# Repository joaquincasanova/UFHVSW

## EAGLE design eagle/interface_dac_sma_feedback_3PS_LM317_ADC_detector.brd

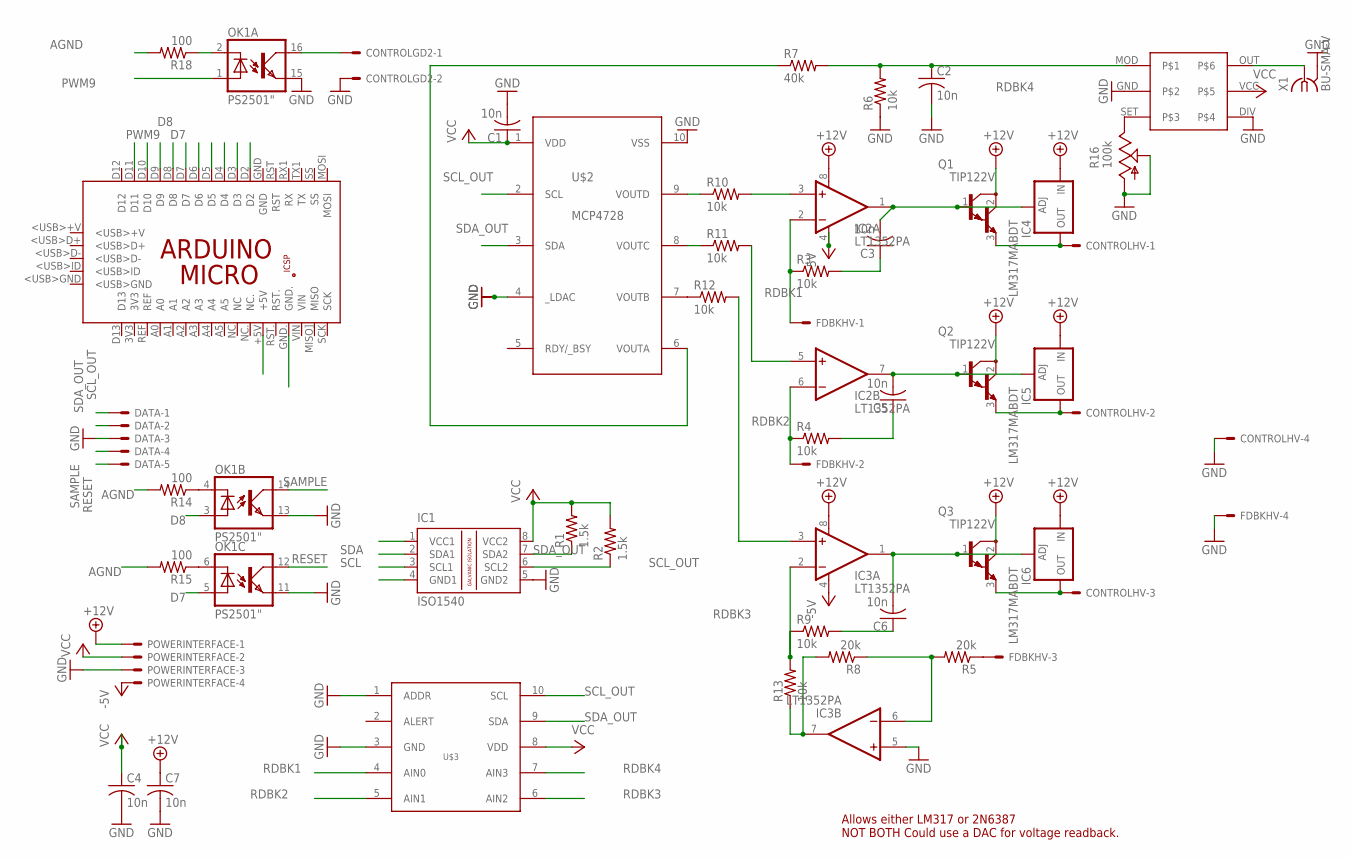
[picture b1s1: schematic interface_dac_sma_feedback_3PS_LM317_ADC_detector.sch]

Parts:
C1, C2, C3, C4, C5, C6, C7: 10n; C050-024X044
CONTROLGD2: KK-156-2
CONTROLHV: KK-156-4
DATA: KK-156-5
FDBKHV: KK-156-4
IC1: ISO1540; DIL08
IC2, IC3: LT1352PA; DIL08
IC4, IC5, IC6: LM317MABDT; DPACK
OK1: PS2501"; DIL16
PCB1: ARDUINO_MICRO
POWERINTERFACE: KK-156-4
Q1, Q2, Q3: TIP122V; TO220V
R1, R2: 1.5k; 0207/12
R3, R4, R6, R9, R10, R11, R12, R13: 10k; 0207/12
R5, R8: 20k; 0207/12
R7: 40k; 0207/12
R14, R15, R18: 100; 0207/12
R16: 100k; SP19L
U$1: LTC6992; DIL06
U$2: MCP4728DIL; DIL10
U$3: ADS1015DIL; DIL10
X1: BU-SMA-V

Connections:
+12V: C7.1, IC2.8 (V+), IC3.8 (V+), IC4.3 (IN), IC5.3 (IN), IC6.3 (IN), POWERINTERFACE.1, Q1.2 (C), Q2.2 (C), Q3.2 (C)
-5V: IC2.4 (V-), IC3.4 (V-), POWERINTERFACE.4
A+5: IC1.1 (VCC1), PCB1.+5V
AGND: IC1.4 (GND1), PCB1.GND., R14.2, R15.2, R18.2
D4: PCB1.D4
D7: OK1.5 (A), PCB1.D7
D8: OK1.3 (A), PCB1.D8
D10: PCB1.D10
D11: PCB1.D11
ENSW2: CONTROLGD2.1, OK1.16 (COL)
GND: C1.2, C2.2, C4.2, C7.2, CONTROLGD2.2, CONTROLHV.4, DATA.3, FDBKHV.4, IC1.5 (GND2), IC3.5 (+IN), OK1.11 (EMI), OK1.13 (EMI), OK1.15 (EMI), POWERINTERFACE.3, R6.1, R16.A, R16.S, U$1.DIV, U$1.GND, U$2.4 (_LDAC), U$2.10 (VSS), U$3.1 (ADDR), U$3.3 (GND), X1.2, X1.3 (2), X1.4 (2), X1.5 (2)
unnamed: R7.1, U$2.6 (VOUTA)
unnamed: OK1.4 (C), R14.1
unnamed: C3.1, R3.2
unnamed: CONTROLHV.1, IC4.4 (OUT), Q1.3 (E)
unnamed: CONTROLHV.3, IC6.4 (OUT), Q3.3 (E)
unnamed: OK1.6 (C), R15.1
unnamed: OK1.2 (C), R18.1
unnamed: FDBKHV.3, R5.1
unnamed: C5.2, IC2.7 (OUT), IC5.1 (ADJ), Q2.1 (B)
unnamed: CONTROLHV.2, IC5.4 (OUT), Q2.3 (E)
unnamed: R16.E, U$1.SET
unnamed: U$1.OUT, X1.1
unnamed: IC3.7 (OUT), R8.2, R13.1
unnamed: C5.1, R4.2
unnamed: IC2.3 (+IN), R10.2
unnamed: IC2.5 (+IN), R11.2
unnamed: IC3.3 (+IN), R12.2
unnamed: C3.2, IC2.1 (OUT), IC4.1 (ADJ), Q1.1 (B)
unnamed: C6.1, R9.2
unnamed: C6.2, IC3.1 (OUT), IC6.1 (ADJ), Q3.1 (B)
unnamed: IC3.6 (-IN), R5.2, R8.1
unnamed: R10.1, U$2.9 (VOUTD)
unnamed: R12.1, U$2.7 (VOUTB)
unnamed: R11.1, U$2.8 (VOUTC)
PWM5: PCB1.D5
PWM6: PCB1.D6
PWM9: OK1.1 (A), PCB1.D9
RDBK1: FDBKHV.1, IC2.2 (-IN), R3.1, U$3.4 (AIN0)
RDBK2: FDBKHV.2, IC2.6 (-IN), R4.1, U$3.5 (AIN1)
RDBK3: IC3.2 (-IN), R9.1, R13.2, U$3.6 (AIN2)
RDBK4: C2.1, R6.2, R7.2, U$1.MOD, U$3.7 (AIN3)
RESET: DATA.5, OK1.12 (COL)
SAMPLE: DATA.4, OK1.14 (COL)
SCL: IC1.3 (SCL1), PCB1.D3
SCL_OUT: DATA.1, IC1.6 (SCL2), R2.1, U$2.2 (SCL), U$3.10 (SCL)
SDA: IC1.2 (SDA1), PCB1.D2
SDA_OUT: DATA.2, IC1.7 (SDA2), R1.1, U$2.3 (SDA), U$3.9 (SDA)
VCC: C1.1, C4.1, IC1.8 (VCC2), POWERINTERFACE.2, R1.2, R2.2, U$1.VCC, U$2.1 (VDD), U$3.8 (VDD)

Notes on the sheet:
Allows either LM317 or 2N6387 NOT BOTH Could use a DAC for voltage readback.

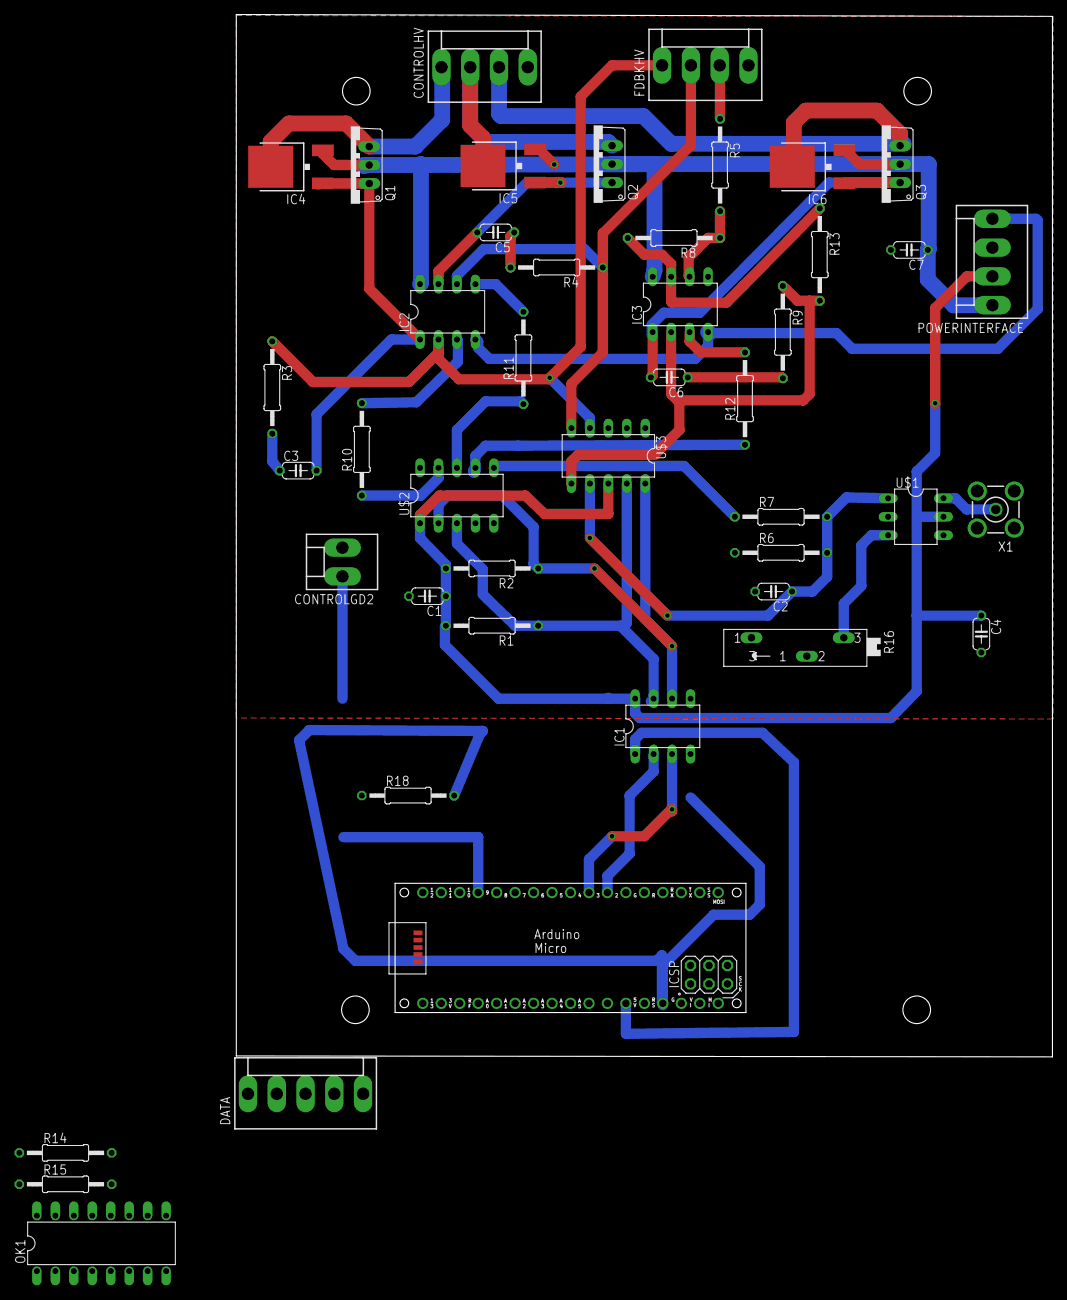
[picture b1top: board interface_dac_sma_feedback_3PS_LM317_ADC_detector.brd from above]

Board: 2 copper layers, 112.3 x 143.4 mm, 44 parts (0 on the bottom side), 44 nets.

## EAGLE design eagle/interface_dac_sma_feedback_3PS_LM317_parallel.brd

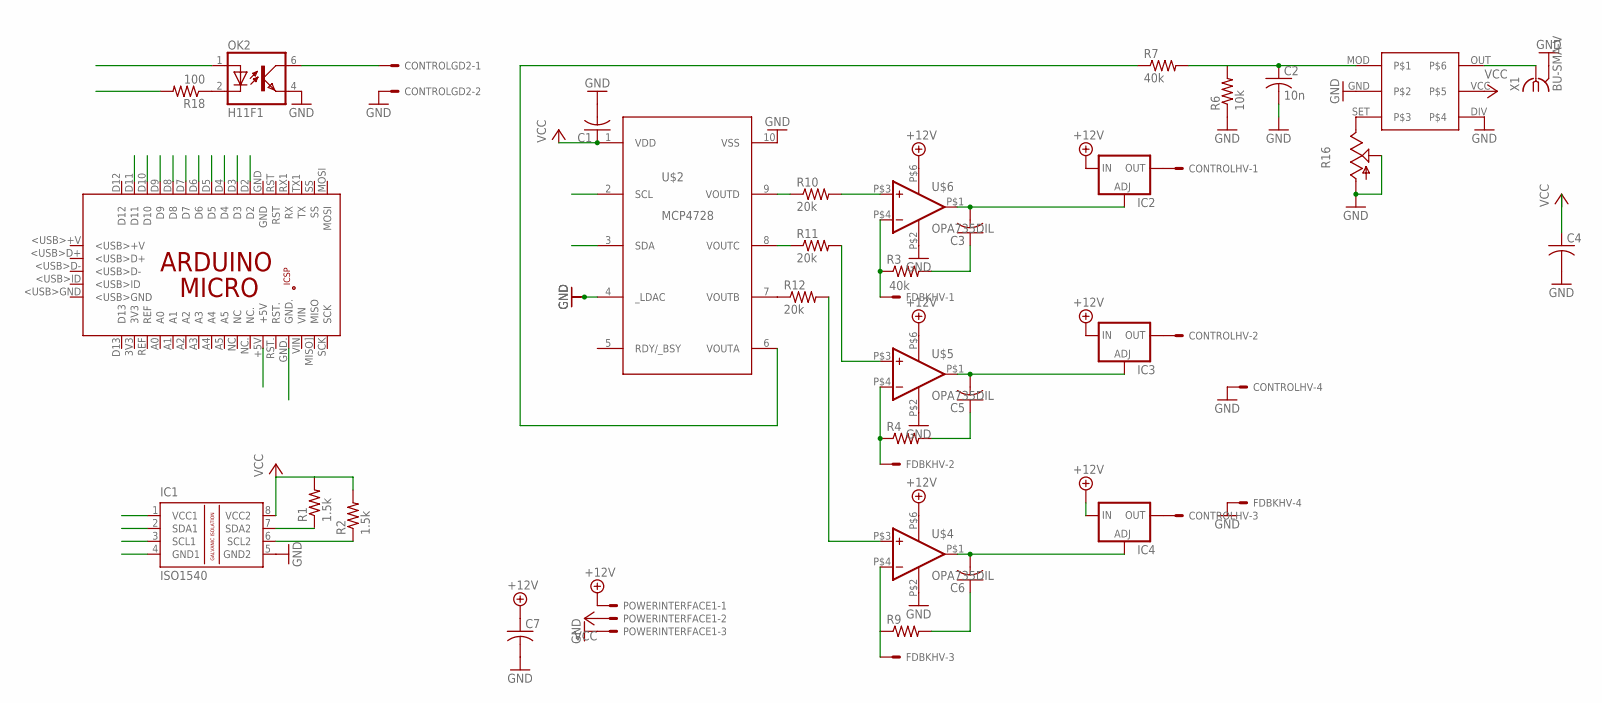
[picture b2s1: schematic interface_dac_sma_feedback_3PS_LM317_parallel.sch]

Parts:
C1, C7: C-US050-050X075; C050-050X075
C2: 10n; C050-024X044
C3, C5, C6: C-US050-024X044; C050-024X044
C4: C-US075-063X106; C075-063X106
CONTROLGD2: KK-156-2
CONTROLHV: KK-156-4
FDBKHV: 40k; KK-156-4
IC1: ISO1540; DIL08
IC2, IC3, IC4: LM317TS; 317TS
OK2: H11F1; DIL05
PCB1: ARDUINO_MICRO
POWERINTERFACE1: KK-156-3
R1, R2: 1.5k; 0207/12
R3, R4, R9: R-US_0207/12; 0207/12
R6: 10k; 0207/12
R7: 40k; 0207/12
R10, R11, R12: 20k; 0207/12
R16: TRIM_US-B90P; SP19L
R18: 100; 0207/12
U$1: LTC6992; DIL06
U$2: MCP4728DIL; DIL10
U$4, U$5, U$6: OPA735DIL; DIL6
X1: BU-SMA-V

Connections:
+12V: C7.1, IC2.3 (IN), IC3.3 (IN), IC4.3 (IN), POWERINTERFACE1.1, U$4.P$6 (V+), U$5.P$6 (V+), U$6.P$6 (V+)
A+5: IC1.1 (VCC1), PCB1.+5V
AGND: IC1.4 (GND1), PCB1.GND., R18.2
D4: PCB1.D4
D7: PCB1.D7
D8: PCB1.D8
D10: PCB1.D10
D11: PCB1.D11
ENSW2: CONTROLGD2.1, OK2.6 (COL)
GND: C1.2, C2.2, C4.2, C7.2, CONTROLGD2.2, CONTROLHV.4, FDBKHV.4, IC1.5 (GND2), OK2.4 (EMIT), POWERINTERFACE1.3, R6.1, R16.A, R16.S, U$1.DIV, U$1.GND, U$2.4 (_LDAC), U$2.10 (VSS), U$4.P$2 (V-), U$5.P$2 (V-), U$6.P$2 (V-), X1.2, X1.3 (2), X1.4 (2), X1.5 (2)
unnamed: R7.1, U$2.6 (VOUTA)
unnamed: C2.1, R6.2, R7.2, U$1.MOD
unnamed: C3.1, R3.2
unnamed: CONTROLHV.1, IC2.2 (OUT)
unnamed: CONTROLHV.3, IC4.2 (OUT)
unnamed: FDBKHV.2, R4.1, U$5.P$4 (-IN)
unnamed: OK2.2 (C), R18.1
unnamed: FDBKHV.1, R3.1, U$6.P$4 (-IN)
unnamed: C5.2, IC3.1 (ADJ), U$5.P$1 (OUT)
unnamed: CONTROLHV.2, IC3.2 (OUT)
unnamed: R16.E, U$1.SET
unnamed: U$1.OUT, X1.1
unnamed: FDBKHV.3, R9.1, U$4.P$4 (-IN)
unnamed: C5.1, R4.2
unnamed: R10.2, U$6.P$3 (+IN)
unnamed: R11.2, U$5.P$3 (+IN)
unnamed: R12.2, U$4.P$3 (+IN)
unnamed: C3.2, IC2.1 (ADJ), U$6.P$1 (OUT)
unnamed: C6.1, R9.2
unnamed: C6.2, IC4.1 (ADJ), U$4.P$1 (OUT)
unnamed: R10.1, U$2.9 (VOUTD)
unnamed: R12.1, U$2.7 (VOUTB)
unnamed: R11.1, U$2.8 (VOUTC)
PWM5: PCB1.D5
PWM6: PCB1.D6
PWM9: OK2.1 (A), PCB1.D9
SCL: IC1.3 (SCL1), PCB1.D3
SCL_OUT: IC1.6 (SCL2), R2.1, U$2.2 (SCL)
SDA: IC1.2 (SDA1), PCB1.D2
SDA_OUT: IC1.7 (SDA2), R1.1, U$2.3 (SDA)
VCC: C1.1, C4.1, IC1.8 (VCC2), POWERINTERFACE1.2, R1.2, R2.2, U$1.VCC, U$2.1 (VDD)

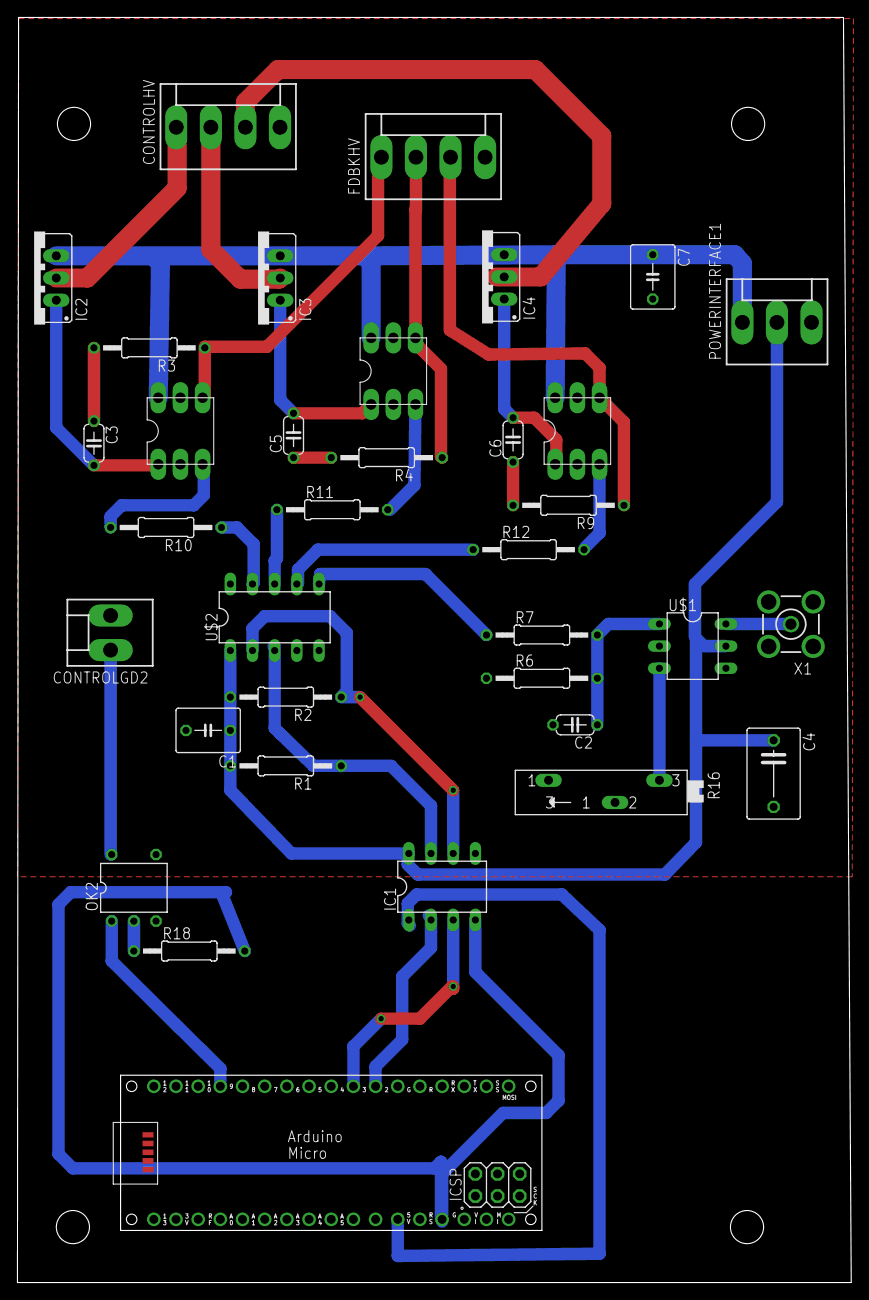
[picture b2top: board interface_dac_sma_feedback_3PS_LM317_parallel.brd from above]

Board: 2 copper layers, 95.5 x 144.9 mm, 35 parts (0 on the bottom side), 34 nets.

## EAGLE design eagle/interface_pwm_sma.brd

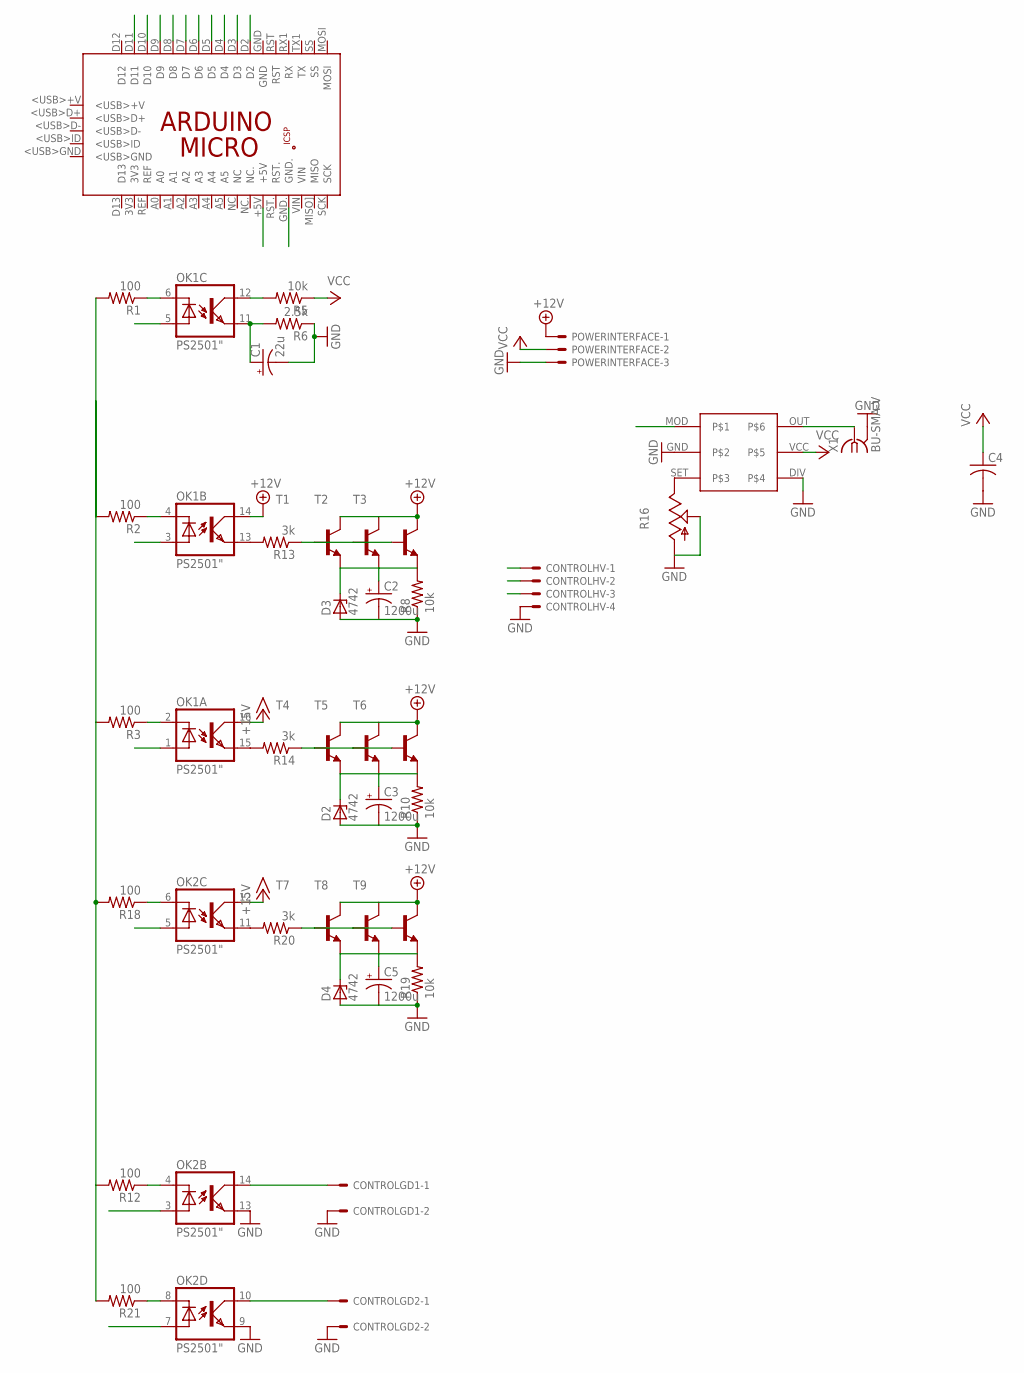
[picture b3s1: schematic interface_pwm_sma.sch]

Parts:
C1: 22u; E5-10,5
C2, C3, C5: 1200u; EB20D
C4: C-US075-063X106; C075-063X106
CONTROLGD1, CONTROLGD2: KK-156-2
CONTROLHV: KK-156-4
D2, D3, D4: 4742; ZDIO-10
OK1, OK2: PS2501"; DIL16
PCB1: ARDUINO_MICRO
POWERINTERFACE: KK-156-3
R1, R2, R3, R12, R18, R21: 100; 0207/12
R5: 10k; 0207/15
R6: 2.5k; 0207/12
R8, R10, R19: 10k; 0207/12
R13, R14, R20: 3k; 0207/15
R16: TRIM_US-B90P; SP19L
T1, T2, T3, T4, T5, T6, T7, T8, T9: 2N2222-NPN-TO92-EBC; TO92-EBC
U$1: LTC6992; DIL06
X1: BU-SMA-V

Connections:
+15V: OK1.14 (COL), OK1.16 (COL), OK2.12 (COL), POWERINTERFACE.1, T1.C, T2.C, T3.C, T4.C, T5.C, T6.C, T7.C, T8.C, T9.C
A+5: PCB1.+5V
AGND: PCB1.GND., R1.2, R2.2, R3.2, R12.2, R18.2, R21.2
D2: PCB1.D2
D4: PCB1.D4
D7: PCB1.D7
D8: OK2.7 (A), PCB1.D8
D10: OK2.3 (A), PCB1.D10
D11: PCB1.D11
ENSW1: CONTROLGD1.1, OK2.14 (COL)
ENSW2: CONTROLGD2.1, OK2.10 (COL)
GND: C1.-, C2.-, C3.-, C4.2, C5.-, CONTROLGD1.2, CONTROLGD2.2, CONTROLHV.4, D2.A, D3.A, D4.A, OK2.9 (EMI), OK2.13 (EMI), POWERINTERFACE.3, R6.1, R8.1, R10.1, R16.A, R16.S, R19.1, U$1.DIV, U$1.GND, X1.2, X1.3 (2), X1.4 (2), X1.5 (2)
unnamed: OK2.4 (C), R12.1
unnamed: OK1.12 (COL), R5.2
unnamed: OK1.6 (C), R1.1
unnamed: OK1.4 (C), R2.1
unnamed: OK1.15 (EMI), R14.2
unnamed: OK2.6 (C), R18.1
unnamed: R20.1, T7.B, T8.B, T9.B
unnamed: OK2.8 (C), R21.1
unnamed: OK1.2 (C), R3.1
unnamed: R16.E, U$1.SET
unnamed: U$1.OUT, X1.1
unnamed: OK1.13 (EMI), R13.2
unnamed: R13.1, T1.B, T2.B, T3.B
unnamed: R14.1, T4.B, T5.B, T6.B
unnamed: OK2.11 (EMI), R20.2
PWM3: OK1.5 (A), PCB1.D3
PWM5: OK1.3 (A), PCB1.D5
PWM6: OK1.1 (A), PCB1.D6
PWM9: OK2.5 (A), PCB1.D9
PWMOUT: C1.+, OK1.11 (EMI), R6.2, U$1.MOD
VCC: C4.1, POWERINTERFACE.2, R5.1, U$1.VCC
VREG1: C2.+, CONTROLHV.1, D3.C, R8.2, T1.E, T2.E, T3.E
VREG2: C3.+, CONTROLHV.2, D2.C, R10.2, T4.E, T5.E, T6.E
VREG3: C5.+, CONTROLHV.3, D4.C, R19.2, T7.E, T8.E, T9.E

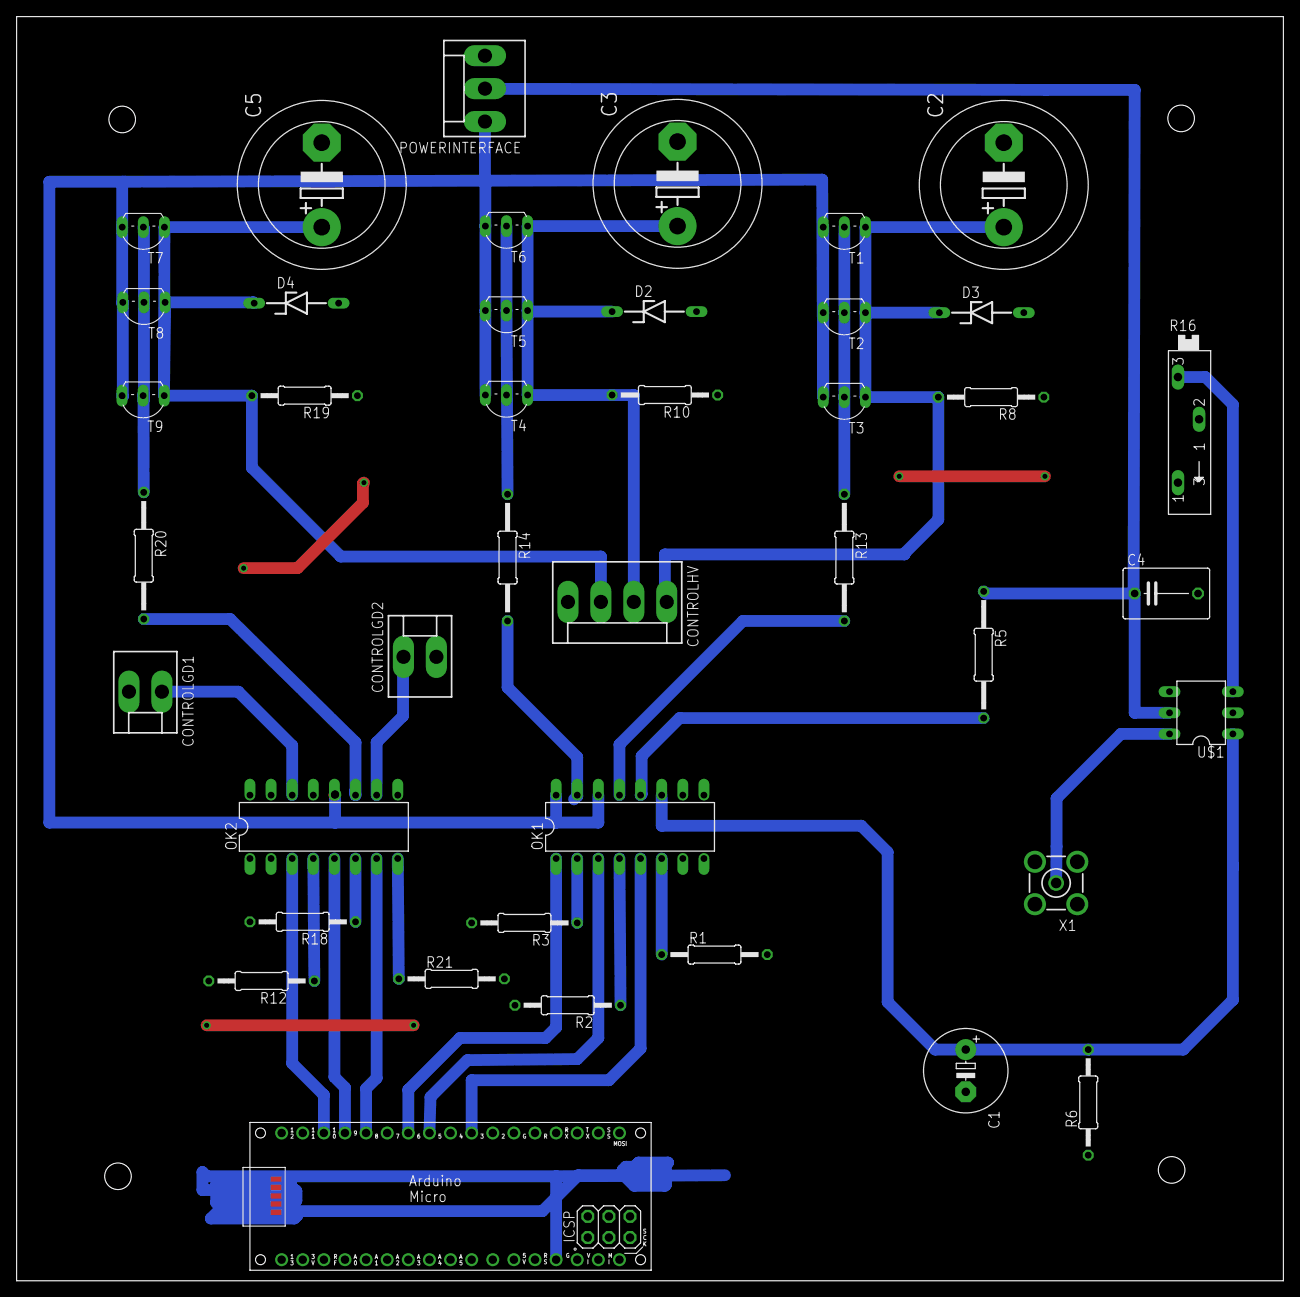
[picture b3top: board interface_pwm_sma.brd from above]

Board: 2 copper layers, 152.4 x 152.1 mm, 41 parts (0 on the bottom side), 31 nets.

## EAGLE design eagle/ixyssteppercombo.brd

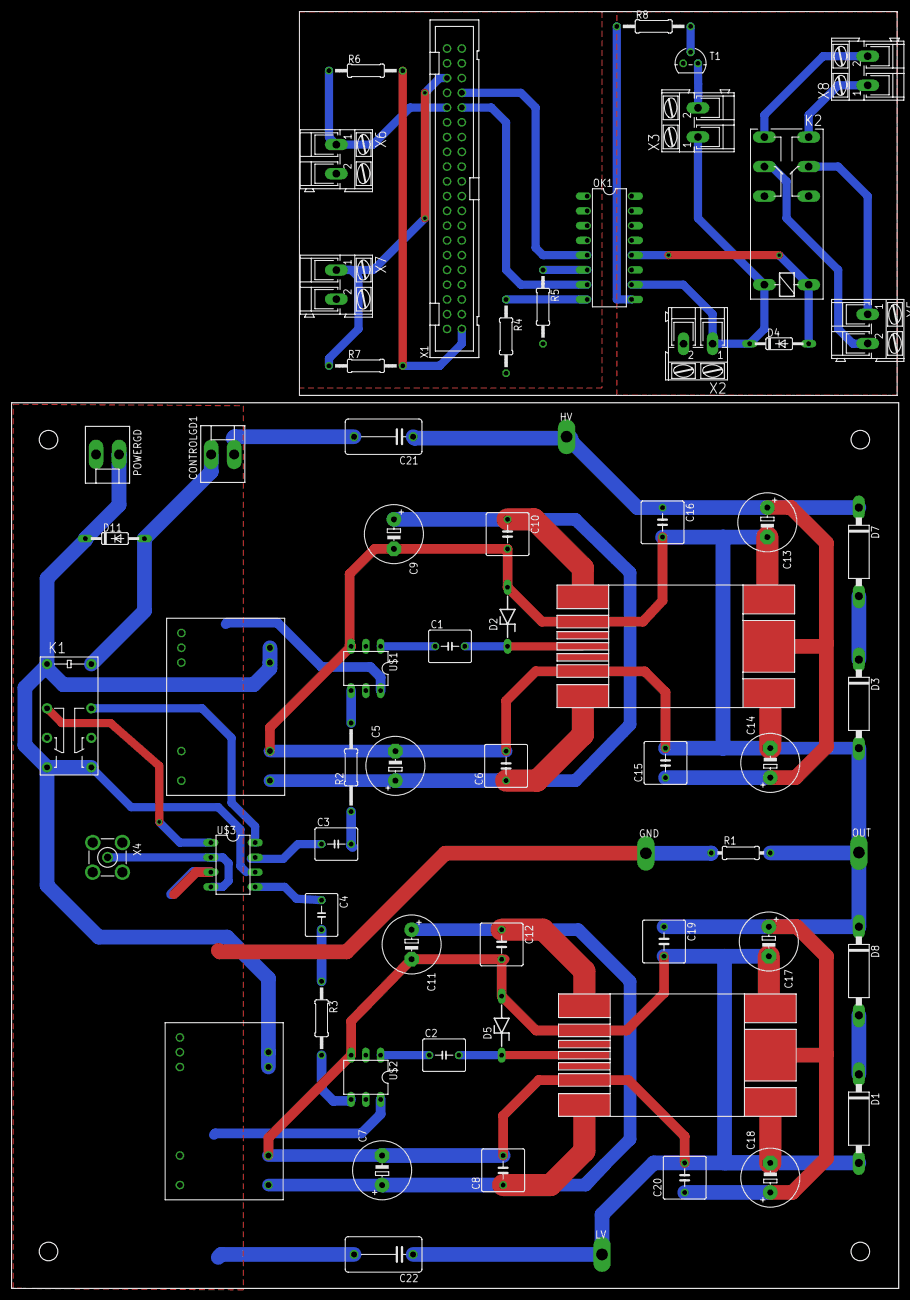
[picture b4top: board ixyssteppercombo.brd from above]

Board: 2 copper layers, 152.7 x 219.7 mm, 63 parts (0 on the bottom side), 43 nets.

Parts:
C1, C2, C3, C4: C050-055X075
C5, C7, C9, C11, C13, C14, C17, C18: E5-10,5
C6, C8, C10, C12, C15, C16, C19, C20: C050-075X075
C21, C22: C102-064X133
CONTROLGD1: KK-156-2
D1, D3, D7, D8: P6KEXXA; C1702-15
D2, D5: 4742; ZDIO-10
D4, D11: 1N4148DO35-10; DO35-10
DC1, DC2: NCS
GND: TPPAD1-20Y; P1-20Y
HV: TPPAD1-20Y; P1-20Y
K1: G5V-2
K2: RP420005; RP420
LV: TPPAD1-20Y; P1-20Y
OK1: PS2501"; DIL16
OUT: TPPAD1-20Y; P1-20Y
POWERGD: KK-156-2
R1: 0207/10
R2: 0207/15
R3, R8: 0207/12
R4, R5: 200; 0207/12
R6, R7: 1k; 0207/12
T1: 2N3904; TO92
U$1, U$2: DA-2319; DIL06
U$3: UCC27425; DIL08
U$8, U$9: IXZ631DF12N100
X1: 2540-; PAK100/2500-40
X2, X3, X5, X6, X7, X8: AK300/2
X4: BU-SMA-V

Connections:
+3V3: R6.2, R7.2, X1.1, X1.17
+5V: X1.2, X1.4
+12V: D11.C, DC1.P$8, DC1.P$9, DC2.P$8, DC2.P$9, K1.1, K1.8, K1.9, POWERGD.1, U$3.6
+24V: D4.C, K2.A2, OK1.10, X2.1, X3.1
ENSW: CONTROLGD1.1, D11.A, K1.16
GND: C21.2, C22.2, CONTROLGD1.2, DC1.P$2, DC1.P$3, DC2.P$2, DC2.P$3, GND.TP, K1.6, K1.11, POWERGD.2, R1.1, U$1.6, U$2.6, U$3.3, X4.2, X4.3, X4.4, X4.5
GND1: R4.2, R5.2, X1.6, X1.9, X1.14, X1.20, X1.25, X1.30, X1.34, X1.39, X6.2, X7.2
GND2: OK1.11, T1.3, X2.2
GPIO6: OK1.7, X1.31
GPIO13: OK1.5, X1.33
unnamed: U$3.2, U$3.4, X4.1
unnamed: C3.1, U$3.7
unnamed: R2.2, U$1.4
unnamed: C4.1, U$3.5
unnamed: R3.2, U$2.4
unnamed: C4.2, R3.1
unnamed: C5.+, C6.1, C9.+, C10.1, DC1.P$6, U$8.P$1, U$8.P$7
unnamed: C7.+, C8.1, C11.+, C12.1, DC2.P$6, U$9.P$1, U$9.P$7
unnamed: D3.C, D7.A
unnamed: C1.1, U$1.1
unnamed: C2.1, U$2.1
unnamed: C1.2, D2.C, U$8.P$4
unnamed: K1.4, U$3.1
unnamed: K1.13, U$3.8
unnamed: C3.2, R2.1
unnamed: C13.+, C14.+, C15.1, C16.1, C21.1, D7.C, HV.TP, U$8.P$9
unnamed: D1.C, D8.A
unnamed: C7.-, C8.2, C11.-, C12.2, C17.-, C18.-, C19.2, C20.2, C22.1, D1.A, D5.A, DC2.P$7, LV.TP, U$2.3, U$9.P$2, U$9.P$6, U$9.P$8, U$9.P$10
unnamed: C5.-, C6.2, C9.-, C10.2, C13.-, C14.-, C15.2, C16.2, C17.+, C18.+, C19.1, C20.1, D2.A, D3.A, D8.C, DC1.P$7, OUT.TP, R1.2, U$1.3, U$8.P$2, U$8.P$6, U$8.P$8, U$8.P$10, U$9.P$9
unnamed: C2.2, D5.C, U$9.P$4
unnamed: OK1.8, R4.1
unnamed: OK1.6, R5.1
unnamed: R6.1, X1.32, X6.1
unnamed: D4.A, K2.A1, OK1.12
unnamed: X1.36, X7.1
unnamed: R7.1, X7.1
unnamed: OK1.9, R8.1
unnamed: T1.1, X3.2
unnamed: R8.2, T1.2
unnamed: K2.11, X5.1
unnamed: K2.14, X8.1
unnamed: K2.21, X5.2
unnamed: K2.24, X8.2

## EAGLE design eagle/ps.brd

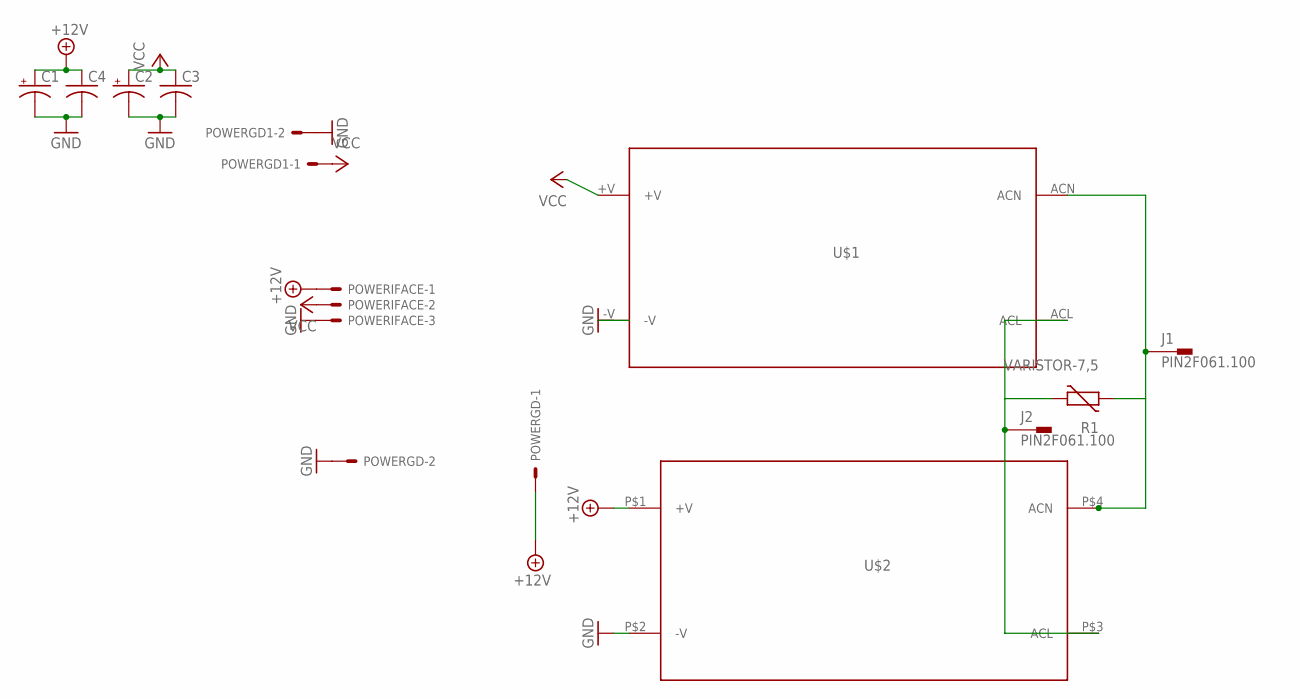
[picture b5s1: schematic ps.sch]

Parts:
C1, C2: CPOL-USE5-13; E5-13
C3, C4: C-US050-050X075; C050-050X075
J1, J2: PIN2F061.100; F061.100
POWERGD, POWERGD1: KK-156-2
POWERIFACE: KK-156-3
R1: VARISTOR-7,5; R-7,5
U$1: IRM-05-05
U$2: IRM-60-12

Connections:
+12V: C1.+, C4.1, POWERGD.1, POWERIFACE.1, U$2.P$1 (+V)
GND: C1.-, C2.-, C3.2, C4.2, POWERGD.2, POWERGD1.2, POWERIFACE.3, U$1.-V, U$2.P$2 (-V)
unnamed: J1.A1, J1.A2, R1.2, U$1.ACN, U$2.P$4 (ACN)
unnamed: J2.A1, J2.A2, R1.1, U$1.ACL, U$2.P$3 (ACL)
VCC: C2.+, C3.1, POWERGD1.1, POWERIFACE.2, U$1.+V

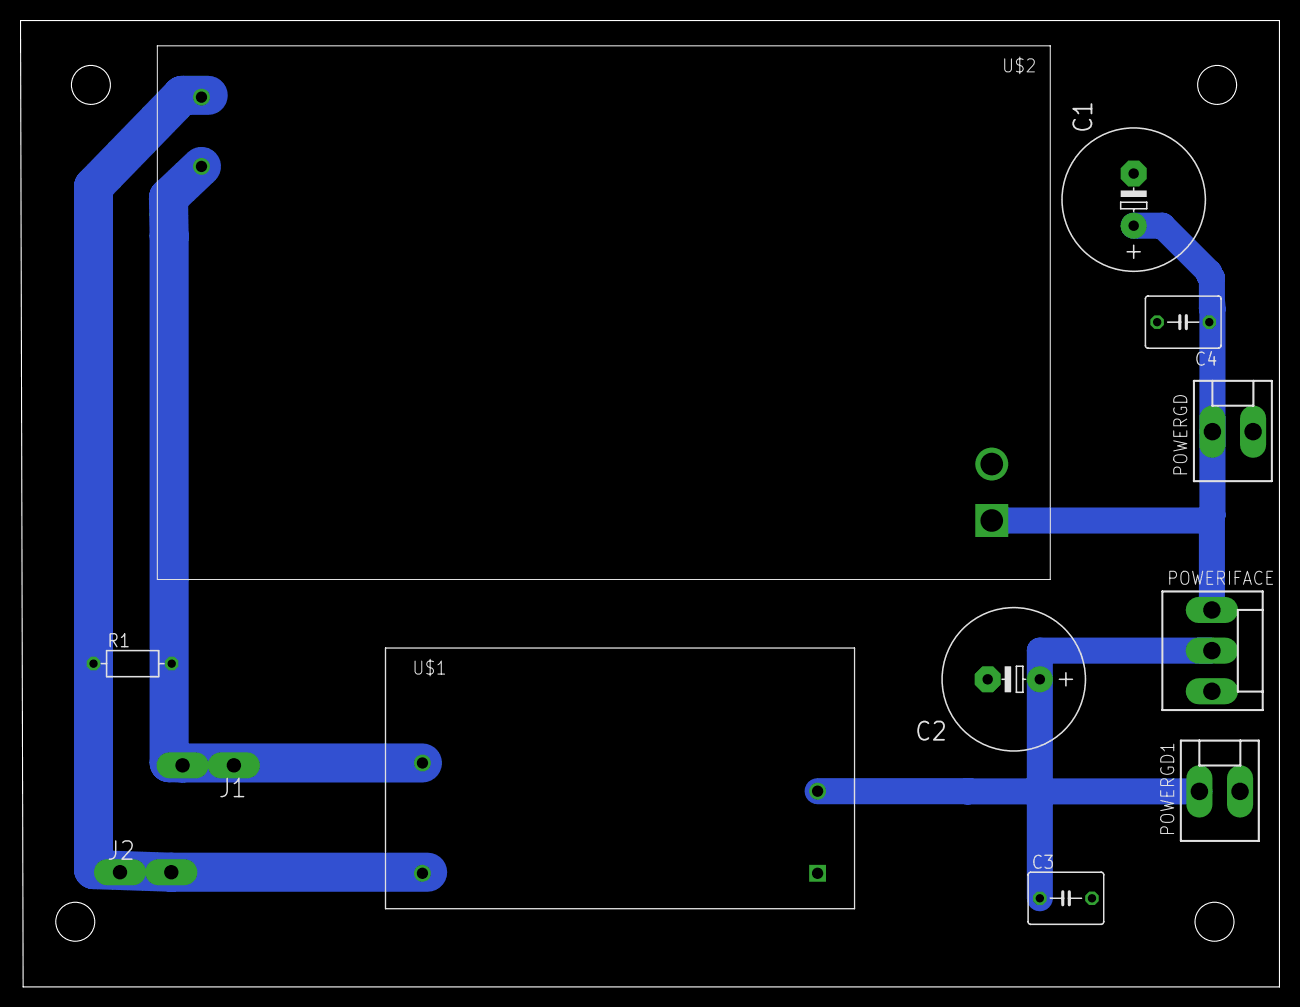
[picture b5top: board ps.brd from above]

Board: 2 copper layers, 122.7 x 94.2 mm, 12 parts (0 on the bottom side), 5 nets.

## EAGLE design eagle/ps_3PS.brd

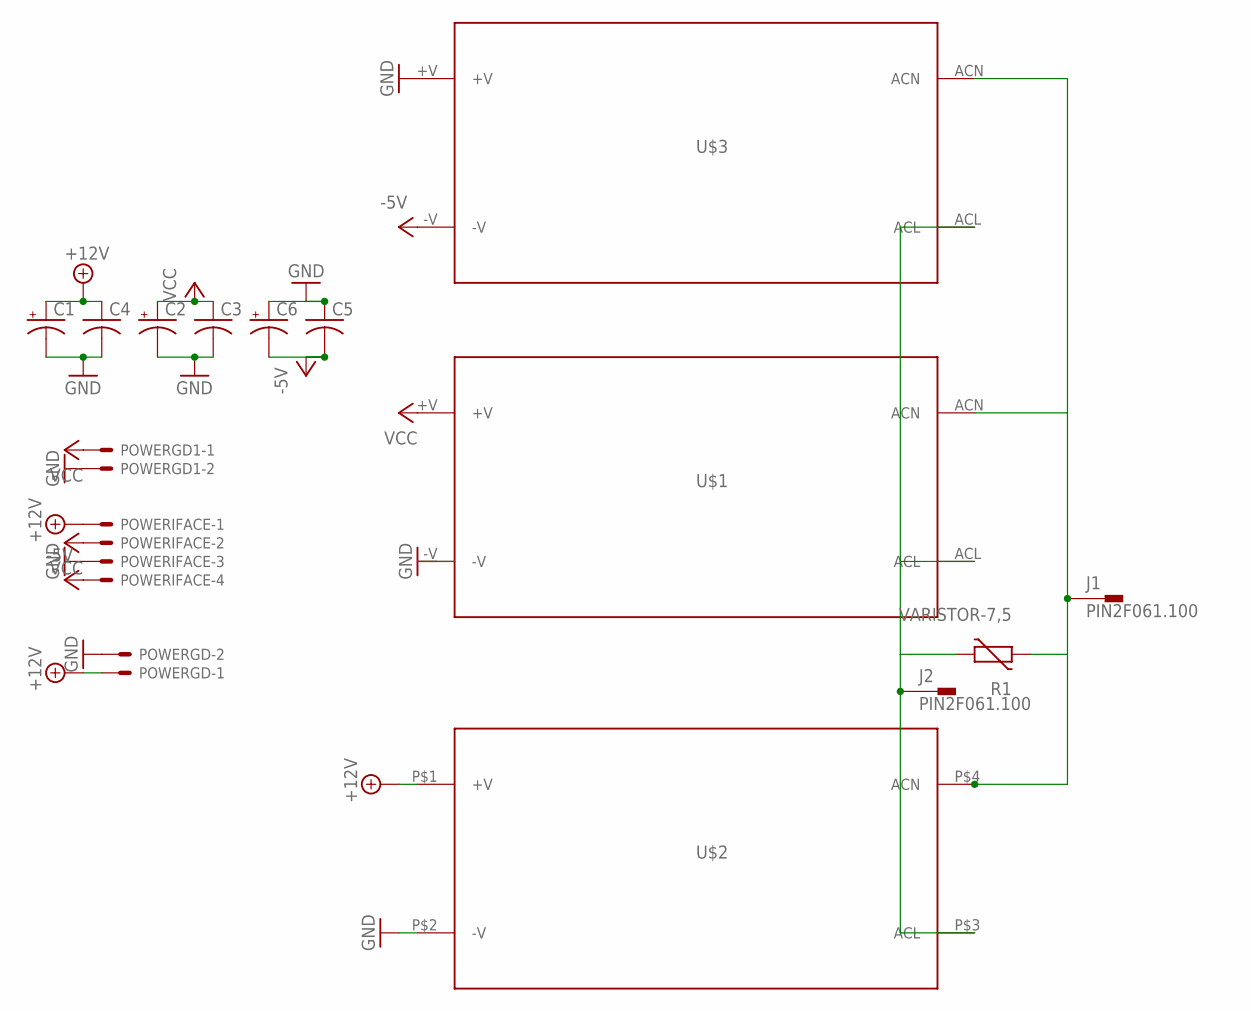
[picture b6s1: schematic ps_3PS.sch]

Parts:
C1, C2, C6: CPOL-USE5-13; E5-13
C3, C4, C5: C-US050-050X075; C050-050X075
J1, J2: PIN2F061.100; F061.100
POWERGD, POWERGD1: KK-156-2
POWERIFACE: KK-156-4
R1: VARISTOR-7,5; R-7,5
U$1, U$3: IRM-05-05
U$2: IRM-60-12

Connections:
+12V: C1.+, C4.1, POWERGD.1, POWERIFACE.1, U$2.P$1 (+V)
-5V: C5.2, C6.-, POWERIFACE.4, U$3.-V
GND: C1.-, C2.-, C3.2, C4.2, C5.1, C6.+, POWERGD.2, POWERGD1.2, POWERIFACE.3, U$1.-V, U$2.P$2 (-V), U$3.+V
unnamed: J1.A1, J1.A2, R1.2, U$1.ACN, U$2.P$4 (ACN), U$3.ACN
unnamed: J2.A1, J2.A2, R1.1, U$1.ACL, U$2.P$3 (ACL), U$3.ACL
VCC: C2.+, C3.1, POWERGD1.1, POWERIFACE.2, U$1.+V

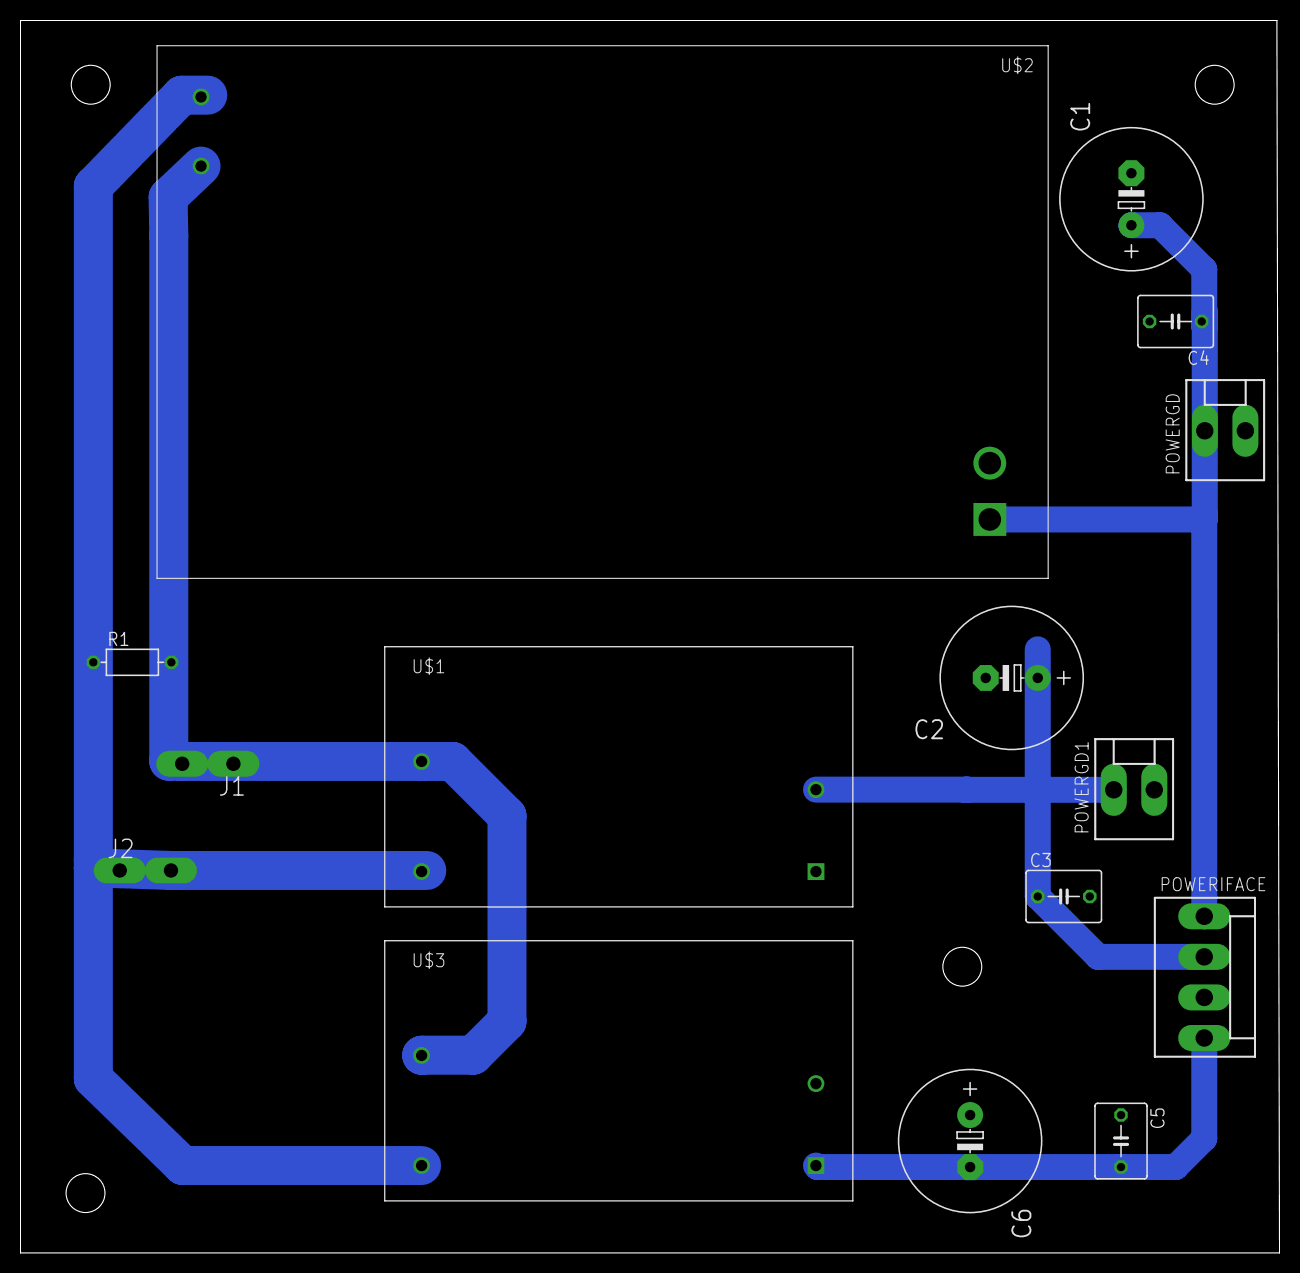
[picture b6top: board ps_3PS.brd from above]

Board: 2 copper layers, 122.9 x 120.3 mm, 15 parts (0 on the bottom side), 6 nets.

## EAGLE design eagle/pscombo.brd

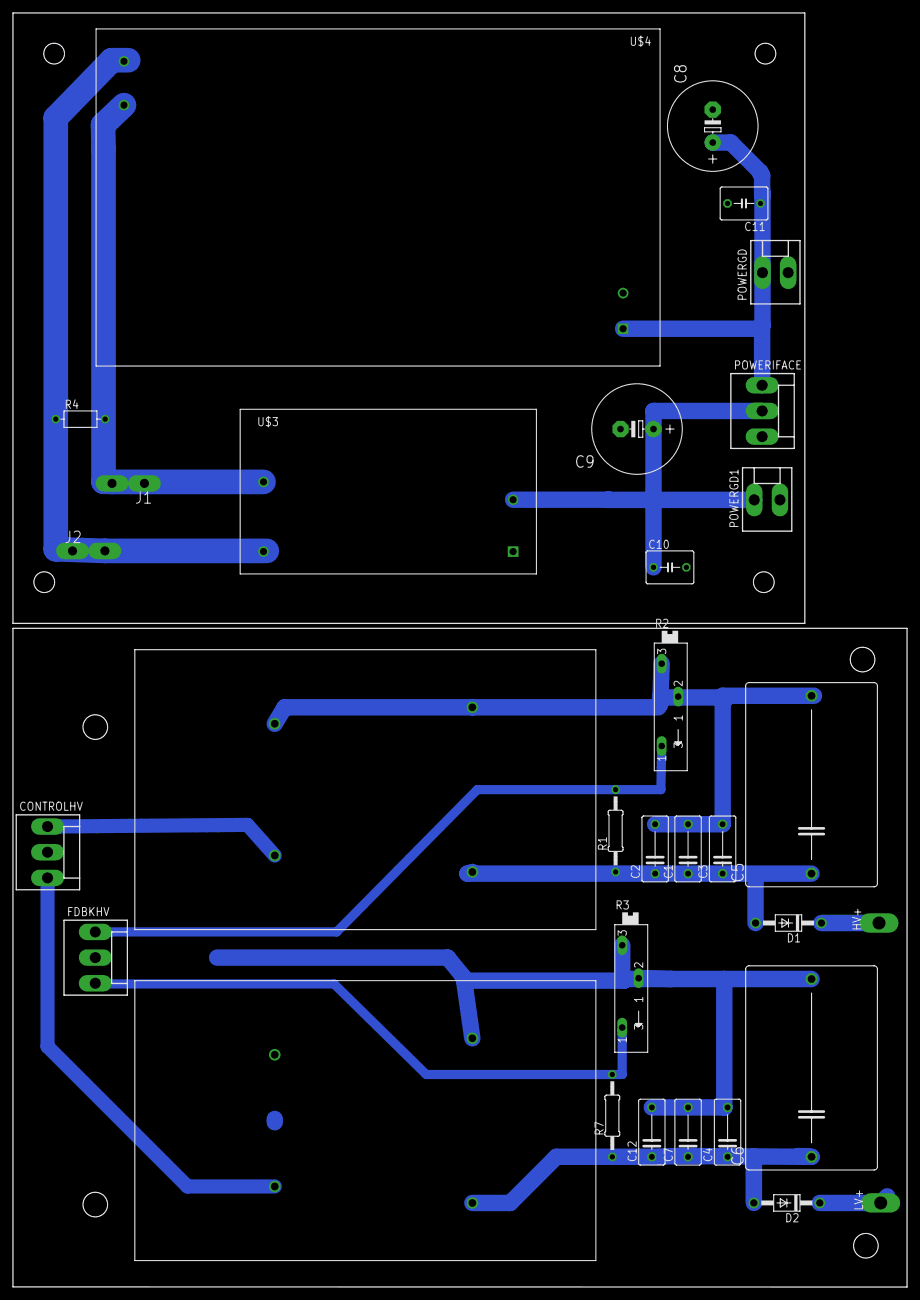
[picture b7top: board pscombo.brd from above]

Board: 2 copper layers, 137.9 x 196.5 mm, 32 parts (0 on the bottom side), 14 nets.

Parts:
C1, C4: 1n; C075-042X103
C2, C7: 10p; C075-042X103
C3, C12: .01u; C075-042X103
C5, C6: 1u; C275-205X316
C8, C9: E5-13
C10, C11: C050-050X075
CONTROLHV: KK-156-3
D1, D2: 1N4004; DO41-10
FDBKHV: KK-156-3
HV+: TPPAD1-20Y; P1-20Y
J1, J2: PIN2F061.100; F061.100
LV+: TPPAD1-20Y; P1-20Y
POWERGD, POWERGD1: KK-156-2
POWERIFACE: KK-156-3
R1, R7: 2M; 0207/12
R2, R3: SP19L
R4: VARISTOR-7,5; R-7,5
U$1, U$2: EMCO-F104PIN; EMCO-F
U$3: IRM-05-05
U$4: IRM-60-12

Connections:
+12V: C8.+, C11.1, POWERGD.1, POWERIFACE.1, U$4.P$1
GND: C1.2, C2.2, C3.2, C4.2, C5.2, C6.2, C7.2, C12.2, CONTROLHV.2, FDBKHV.2, R2.E, R2.S, R3.E, R3.S, U$1.P$2, U$1.P$4, U$2.P$2, U$2.P$4
GND1: C8.-, C9.-, C10.2, C11.2, POWERGD.2, POWERGD1.2, POWERIFACE.3, U$3.-V, U$4.P$2
unnamed: C1.1, C2.1, C3.1, C5.1, D1.A, R1.1, U$1.P$3
unnamed: C4.1, C6.1, C7.1, C12.1, D2.A, R7.1, U$2.P$3
unnamed: FDBKHV.1, R1.2, R2.A
unnamed: CONTROLHV.1, U$1.P$1
unnamed: CONTROLHV.3, U$2.P$1
unnamed: D1.C, HV+.TP
unnamed: D2.C, LV+.TP
unnamed: FDBKHV.3, R3.A, R7.2
unnamed: J1.A1, J1.A2, R4.2, U$3.ACN, U$4.P$4
unnamed: J2.A1, J2.A2, R4.1, U$3.ACL, U$4.P$3
VCC: C9.+, C10.1, POWERGD1.1, POWERIFACE.2, U$3.+V
